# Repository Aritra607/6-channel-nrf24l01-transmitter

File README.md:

# 6-Channel nRF24L01 Wireless Transmitter

**A professional 6-channel wireless RC transmitter using Arduino Nano and nRF24L01+ RF module for remote control of drones, robots, and RC vehicles.**

> Built at **National Institute of Technology Agartala** | Apr 2025 - Present

---

## 📸 Project Gallery

The system provides precision analog control with reliable 2.4 GHz wireless communication.

| **3D PCB View** | **PCB Layout** | **Circuit Schematic** |
|:---:|:---:|:---:|
|  |  |  |
| *3D render of transmitter PCB* | *Double-sided PCB design* | *Complete circuit diagram* |
| **Transmitter** | **Receiver** |
|:---:|:---:|
|  |  |
| *Transmitter Front* | *Receiver Front* |

---

## 🛠️ Hardware Components

The transmitter is built around the Arduino Nano platform with nRF24L01+ RF module for robust wireless communication.

### Core Components

| Component | Specification | Quantity | Description |
| :--- | :--- | :---: | :--- |
| **Microcontroller** | Arduino Nano (ATmega328P) | 1 | 5V/16MHz processing |
| **RF Module** | nRF24L01+ | 1 | 2.4 GHz transceiver |
| **Joysticks** | Dual-axis analog | 3 | 6-axis control input |
| **Power Supply** | 5V regulated | 1 | USB or 7-12V battery input |
| **Decoupling Capacitors** | 10µF + 100nF | Multiple | Power stability for nRF24L01 |

### Input Configuration

| Channel | Analog Pin | Function | Control Type |
|:-------:|:----------:|:---------|:-------------|
| **CH1** | A0 | Throttle | Joystick Y-axis |
| **CH2** | A1 | Yaw | Joystick X-axis |
| **CH3** | A2 | Pitch | Joystick Y-axis |
| **CH4** | A3 | Roll | Joystick X-axis |
| **CH5** | A6 | AUX1 | Joystick Y-axis / Potentiometer |
| **CH6** | A7 | AUX2 | Joystick Y-axis / Potentiometer |

---

## 🚀 Key Features

* **6-Channel Control:** Full 6-axis control for complex RC applications
* **2.4 GHz Communication:** nRF24L01+ module with 100+ meter range (with antenna)
* **Low Latency:** 250 kbps data rate for responsive control
* **Precision Input:** 8-bit resolution (0-255) per channel
* **Auto Calibration:** Software joystick center-point mapping
* **Failsafe Mode:** Automatic safe position on signal loss
* **Low Power:** Efficient power consumption for extended battery life
* **Bi-directional Capable:** nRF24L01 supports two-way communication (receiver can send telemetry back)
* **Pipe Addressing:** Unique 40-bit address prevents crosstalk between multiple systems
* **SPI Communication:** Fast interfacing with Arduino

---

## 🏗️ Technical Architecture

The system uses the **nRF24L01+ RF module** with Arduino Nano for digital wireless data transmission.

### System Operation Flow

1. **Analog Reading:** Arduino reads 6 analog inputs from joysticks (A0-A3, A6, A7)
2. **Data Mapping:** Raw ADC values (0-1023) mapped to 0-255 range with center calibration
3. **Packet Formation:** Six 8-bit values packed into Signal structure (6 bytes total)
4. **RF Transmission:** nRF24L01 transmits packet at 250 kbps via 2.4 GHz radio
5. **Continuous Loop:** Transmitter sends updated data continuously (~100 Hz typical)

### Communication Protocol

**Pipe Address:** `0xE9E8F0F0E1LL` (40-bit unique identifier)
**Data Rate:** 250 kbps (long range mode)
**Power Level:** RF24_PA_HIGH (maximum transmission power)
**Auto-Acknowledgment:** Disabled for minimal latency
**Packet Size:** 6 bytes per transmission

### Signal Structure

```cpp
struct Signal {
  byte throttle;  // 0-255 (12 = motor stop on signal loss)
  byte pitch;     // 0-255 (127 = center)
  byte roll;      // 0-255 (127 = center)
  byte yaw;       // 0-255 (127 = center)
  byte aux1;      // 0-255 (127 = center)
  byte aux2;      // 0-255 (127 = center)
};
```

### Failsafe Configuration

On signal loss, receiver defaults to:
- **Throttle:** 12 (motor stop)
- **All other channels:** 127 (center position)

---

## 💻 Getting Started

### Prerequisites

* **Arduino IDE** (1.8.x or later) - [Download here](https://www.arduino.cc/en/software)
* **RF24 Library** by TMRh20 - Install via Library Manager
* **Arduino Nano** with USB cable
* **nRF24L01+ Module** (preferably with external antenna)
* Basic soldering equipment
* 6 analog joysticks or potentiometers
* 5V regulated power supply

### 1. Clone the Repository

```bash
git clone https://github.com/Aritra607/6-channel-nrf24l01-transmitter.git
cd 6-channel-nrf24l01-transmitter
```

### 2. Install Arduino Libraries

#### Method 1: Arduino Library Manager (Recommended)

1. Open Arduino IDE
2. Go to **Sketch → Include Library → Manage Libraries**
3. Search for "RF24"
4. Install **"RF24 by TMRh20"**
5. Restart Arduino IDE

#### Method 2: Manual Installation

```bash
cd ~/Documents/Arduino/libraries/
git clone https://github.com/nRF24/RF24.git
```

### 3. Hardware Assembly

#### 3.1 nRF24L01 to Arduino Nano Wiring

| nRF24L01 Pin | Arduino Nano Pin | Description |
|:------------:|:----------------:|:------------|
| VCC | 3.3V | **IMPORTANT: 3.3V ONLY!** |
| GND | GND | Ground |
| CE | D9 | Chip Enable |
| CSN | D10 | SPI Chip Select |
| SCK | D13 | SPI Clock |
| MOSI | D11 | SPI Master Out |
| MISO | D12 | SPI Master In |
| IRQ | Not connected | Interrupt (optional) |

**⚠️ CRITICAL:** nRF24L01 operates at **3.3V only**. Connecting to 5V will damage the module!

**Power Stability:**
- Add 10µF electrolytic capacitor between VCC and GND (near nRF24L01)
- Add 100nF ceramic capacitor between VCC and GND
- Use short wires to minimize voltage drop

#### 3.2 Joystick Connections

Connect 3 dual-axis analog joysticks to Arduino analog pins:

| Joystick | X-Axis Pin | Y-Axis Pin | VCC | GND | Function |
|:--------:|:----------:|:----------:|:---:|:---:|:---------|
| **Joystick 1** | A1 | A0 | 5V | GND | Yaw (X) / Throttle (Y) |
| **Joystick 2** | A3 | A2 | 5V | GND | Roll (X) / Pitch (Y) |
| **Joystick 3** | A7 | A6 | 5V | GND | AUX2 (X) / AUX1 (Y) |

**Note:** Potentiometers can be used instead of joysticks for AUX channels.

### 4. Software Setup

#### 4.1 Upload Transmitter Code

1. Open `transmitter.ino` in Arduino IDE
2. Select **Tools → Board → Arduino Nano**
3. Select **Tools → Processor → ATmega328P (Old Bootloader)** if needed
4. Select correct COM port under **Tools → Port**
5. Click **Upload** (Ctrl+U)

#### 4.2 Configure Pipe Address

⚠️ **IMPORTANT:** The pipe address in transmitter code **MUST** match the receiver:

```cpp
const uint64_t pipeOut = 0xE9E8F0F0E1LL;
```

If you have multiple systems operating nearby, change this address to a unique value on both TX and RX.

#### 4.3 Calibrate Joysticks

The code auto-calibrates joystick center points. If you experience drift:

1. Measure actual analog values using Serial Monitor:
   ```cpp
   Serial.begin(9600);
   Serial.println(analogRead(A0)); // Repeat for each channel
   ```

2. Adjust mapping values in code:
   ```cpp
   // Example: If your joystick reads 510-515 at center instead of 524
   data.throttle = mapJoystickValues(analogRead(A0), 12, 512, 1020, true);
   ```

3. Test all channels and adjust `lower`, `middle`, `upper` values as needed

### 5. Testing & Verification

#### 5.1 Power-On Test

1. Connect Arduino Nano to USB power
2. **Green LED** on Arduino should light up (power indicator)
3. **Green LED** on nRF24L01 should light up

#### 5.2 Transmission Test (requires receiver)

1. Build or acquire compatible receiver (see Receiver section below)
2. Power on both transmitter and receiver
3. Move joysticks and verify receiver response
4. Test all 6 channels individually
5. Test failsafe by powering off transmitter

#### 5.3 Range Test

1. Start with units 1 meter apart
2. Gradually increase distance
3. Monitor signal reliability
4. Expected range: **100+ meters** with external antenna in open space
5. **50+ meters** with built-in PCB antenna

---

## 📂 Project Structure

```
6-channel-nrf24l01-transmitter/
│
├── transmitter/
│   ├── transmitter.ino              # Main Arduino sketch
│   ├── Gerber_files/                # PCB manufacturing files
│   │   ├── *.GTL                    # Top copper layer
│   │   ├── *.GBL                    # Bottom copper layer
│   │   ├── *.GTO                    # Top silkscreen
│   │   ├── *.GBO                    # Bottom silkscreen
│   │   ├── *.GTS                    # Top soldermask
│   │   ├── *.GBS                    # Bottom soldermask
│   │   └── *.TXT                    # Drill file
│   │
│   └── images/
│       ├── 3D-VIEW.png              # 3D PCB render
│       ├── PCB.png                  # PCB layout view
│       └── Schematics.png           # Circuit schemati
│
├── docs/
│   ├── datasheets/
│   │   ├── nRF24L01.pdf            # RF module datasheet
│   │   ├── ATmega328P.pdf          # Microcontroller datasheet
│   │   └── RF24_Library.pdf        # Library documentation
│   │
│   ├── ASSEMBLY_GUIDE.md            # Detailed build instructions
│   ├── CALIBRATION.md               # Joystick calibration guide
│   ├── PCB_FABRICATION.md           # PCB ordering guide
│   └── TROUBLESHOOTING.md           # Common issues and fixes
│
├── hardware/
│   ├── BOM.md                       # Bill of materials
│   └── transmitter.kicad_pcb        # KiCad PCB design file
│
├── README.md                         # This file
├── LICENSE                           # MIT License
└── .gitignore
```

---

## 🔐 Communication Protocol Details

### nRF24L01+ Configuration

```cpp
radio.setAutoAck(false);           // Disabled for low latency
radio.setDataRate(RF24_250KBPS);   // Long range, lower speed
radio.setPALevel(RF24_PA_HIGH);    // Maximum transmission power
radio.stopListening();             // TX mode only
```

### Channel Mapping Logic

The `mapJoystickValues()` function provides:
- **Dead-zone compensation:** Smooth center-point handling
- **Range calibration:** Maps 10-bit ADC (0-1023) to 8-bit output (0-255)
- **Direction reversal:** Configurable per channel via boolean flag
- **Boundary protection:** Constrain prevents out-of-range values

**Mapping Parameters:**
- `lower`: Minimum joystick ADC value (typically 12)
- `middle`: Center position ADC value (typically 512-524)
- `upper`: Maximum joystick ADC value (typically 1020-1023)
- `reverse`: Invert signal direction (true/false)

### Data Packet Format

Each transmission contains 6 bytes:

```
Byte 0: Throttle (0-255)
Byte 1: Pitch    (0-255)
Byte 2: Roll     (0-255)
Byte 3: Yaw      (0-255)
Byte 4: AUX1     (0-255)
Byte 5: AUX2     (0-255)
```

Transmission rate: ~100 packets/second

---

## 💡 Applications

### 1. **Quadcopter/Drone Control**
Full 6-channel control for throttle, pitch, roll, yaw, plus two auxiliary channels for camera gimbal, lights, or flight modes.

### 2. **RC Car/Tank**
Control steering, throttle, and additional functions like headlights, horn, or weapon systems.

### 3. **Robotic Arm**
Simultaneous control of multiple servo motors for precise manipulation.

### 4. **Camera Gimbal**
Multi-axis camera stabilization and positioning control.

### 5. **RC Boat**
Throttle, rudder control, and auxiliary functions for navigation lights or bilge pump.

### 6. **Educational Platform**
Learn wireless communication, embedded systems, and control systems fundamentals.

---

## 📡 Receiver Setup

This transmitter requires a compatible receiver. Here's a basic receiver code structure:

```cpp
#include <SPI.h>
#include <nRF24L01.h>
#include <RF24.h>
#include <Servo.h>

const uint64_t pipeIn = 0xE9E8F0F0E1LL; // Must match transmitter!
RF24 radio(9, 10);

struct Signal {
  byte throttle;
  byte pitch;
  byte roll;
  byte yaw;
  byte aux1;
  byte aux2;
};

Signal data;
Servo servo1, servo2, servo3, servo4, servo5, servo6;

void setup() {
  radio.begin();
  radio.openReadingPipe(1, pipeIn);
  radio.setAutoAck(false);
  radio.setDataRate(RF24_250KBPS);
  radio.setPALevel(RF24_PA_HIGH);
  radio.startListening(); // Receiver mode
  
  // Attach servos to PWM pins
  servo1.attach(3);  // Throttle/ESC
  servo2.attach(4);  // Pitch
  servo3.attach(5);  // Roll
  servo4.attach(6);  // Yaw
  servo5.attach(7);  // AUX1
  servo6.attach(8);  // AUX2
}

void loop() {
  if (radio.available()) {
    radio.read(&data, sizeof(Signal));
    
    // Map 0-255 to servo pulse width (1000-2000 µs)
    servo1.writeMicroseconds(map(data.throttle, 0, 255, 1000, 2000));
    servo2.writeMicroseconds(map(data.pitch, 0, 255, 1000, 2000));
    servo3.writeMicroseconds(map(data.roll, 0, 255, 1000, 2000));
    servo4.writeMicroseconds(map(data.yaw, 0, 255, 1000, 2000));
    servo5.writeMicroseconds(map(data.aux1, 0, 255, 1000, 2000));
    servo6.writeMicroseconds(map(data.aux2, 0, 255, 1000, 2000));
  }
}
```

**Create a separate receiver project** with this code or download from the repository.

---

## 🔧 Advanced Configuration

### Changing Transmission Power

Adjust range vs power consumption:

```cpp
// Maximum range, higher power consumption
radio.setPALevel(RF24_PA_HIGH);

// Medium range, balanced
radio.setPALevel(RF24_PA_LOW);

// Minimum power for short range
radio.setPALevel(RF24_PA_MIN);
```

### Changing Data Rate

Trade speed for range:

```cpp
// Long range, lower speed (RECOMMENDED)
radio.setDataRate(RF24_250KBPS);

// Balanced
radio.setDataRate(RF24_1MBPS);

// Short range, high speed
radio.setDataRate(RF24_2MBPS);
```

### Reversing Channel Direction

Change the `reverse` parameter in `mapJoystickValues()`:

```cpp
// Normal direction
data.throttle = mapJoystickValues(analogRead(A0), 12, 524, 1020, false);

// Reversed direction
data.throttle = mapJoystickValues(analogRead(A0), 12, 524, 1020, true);
```

### Custom Failsafe Values

Modify `ResetData()` function:

```cpp
void ResetData() {
  data.throttle = 0;      // Full motor stop
  data.pitch = 127;       // Level flight
  data.roll = 127;        // Wings level
  data.yaw = 127;         // No rotation
  data.aux1 = 0;          // Lights off
  data.aux2 = 255;        // Emergency mode active
}
```

---

## 🛠️ Building from Source

### PCB Fabrication

1. **Download Gerber files** from `Gerber_files/` folder
2. **Upload to PCB manufacturer**:
   - Recommended: JLCPCB, PCBWay, OSH Park
   - Board thickness: 1.6mm
   - Finish: HASL or ENIG
   - Color: Your choice (green is cheapest)
3. **Order PCBs** (minimum order typically 5 pieces)
4. **Expected cost:** $2-5 for 5 PCBs + shipping

### Component Assembly

**Soldering Order:**
1. SMD components first (if any)
2. IC sockets (recommended for Arduino and nRF24L01)
3. Resistors
4. Capacitors (mind polarity on electrolytics!)
5. Pin headers for joysticks
6. Arduino Nano socket/header pins
7. nRF24L01 socket/header pins
8. Power connector

**Quality Check:**
- Visual inspection for solder bridges
- Continuity test with multimeter
- Check all power rails (3.3V and 5V)
- Verify no shorts between VCC and GND

---

## 🧪 Joystick Calibration

### Finding Center Values

1. Upload this calibration sketch:

```cpp
void setup() {
  Serial.begin(9600);
}

void loop() {
  Serial.print("A0: "); Serial.print(analogRead(A0));
  Serial.print(" | A1: "); Serial.print(analogRead(A1));
  Serial.print(" | A2: "); Serial.print(analogRead(A2));
  Serial.print(" | A3: "); Serial.print(analogRead(A3));
  Serial.print(" | A6: "); Serial.print(analogRead(A6));
  Serial.print(" | A7: "); Serial.println(analogRead(A7));
  delay(200);
}
```

2. Open Serial Monitor (9600 baud)
3. Center all joysticks
4. Note the center values (typically 500-530)
5. Move joysticks to extremes and note min/max values

### Updating Calibration

Replace values in main code:

```cpp
// Example: If your joystick center reads 515 instead of 524
data.throttle = mapJoystickValues(analogRead(A0), 10, 515, 1023, true);
```

---

## 🔍 Troubleshooting

| **Problem** | **Possible Cause** | **Solution** |
|-------------|-------------------|--------------|
| Transmitter not powering on | Power supply issue | Check USB connection or battery voltage |
| No RF transmission | nRF24L01 damaged | Check 3.3V supply, replace module if needed |
| Erratic behavior | Poor nRF24L01 power | Add 10µF + 100nF capacitors, use short wires |
| Receiver not responding | Pipe address mismatch | Verify `pipeOut` matches receiver's `pipeIn` |
| Short range (<10m) | Missing antenna | Add external antenna or use nRF24L01+PA+LNA |
| Joystick drift | Poor calibration | Re-calibrate center values using Serial Monitor |
| One channel not working | Wiring error | Check joystick connections to analog pins |
| Upload fails | Wrong board/port | Select Arduino Nano and correct COM port |
| Code won't compile | Missing RF24 library | Install RF24 library via Library Manager |
| Interference issues | Channel conflict | Change nRF24L01 channel or pipe address |

### Advanced Diagnostics

Add debug output to Serial Monitor:

```cpp
void setup() {
  Serial.begin(9600);
  radio.begin();
  
  // Check if radio hardware is responding
  if (!radio.isChipConnected()) {
    Serial.println("nRF24L01 NOT detected!");
  } else {
    Serial.println("nRF24L01 initialized successfully");
  }
}

void loop() {
  // Print channel values
  Serial.print("THR:"); Serial.print(data.throttle);
  Serial.print(" | YAW:"); Serial.print(data.yaw);
  Serial.print(" | PIT:"); Serial.print(data.pitch);
  Serial.print(" | ROL:"); Serial.print(data.roll);
  Serial.print(" | AX1:"); Serial.print(data.aux1);
  Serial.print(" | AX2:"); Serial.println(data.aux2);
  
  radio.write(&data, sizeof(Signal));
  delay(50);
}
```

---

## 🎯 Performance Specifications

| Parameter | Value | Notes |
|:----------|:------|:------|
| **Operating Frequency** | 2.400 - 2.525 GHz | ISM band, license-free |
| **Data Rate** | 250 kbps | Configured for maximum range |
| **Transmission Power** | 0 dBm (1 mW) | PA_HIGH setting |
| **Operating Range** | 100m+ (outdoor) | With external antenna |
| **Indoor Range** | 30-50m | Depends on obstacles |
| **Channel Resolution** | 8-bit (256 steps) | Per channel |
| **Update Rate** | ~100 Hz | Limited by loop speed |
| **Supply Voltage** | 5V (Arduino) / 3.3V (nRF24L01) | Regulated required |
| **Current Consumption** | ~50-80 mA | TX + Arduino + joysticks |
| **Battery Life** | 6-10 hours | With 500 mAh battery |

---

## 🔄 Adding More Channels

To expand beyond 6 channels:

1. **Add more analog inputs** (Arduino Nano has A4, A5 available)
2. **Update Signal structure**:
   ```cpp
   struct Signal {
     byte throttle;
     byte pitch;
     byte roll;
     byte yaw;
     byte aux1;
     byte aux2;
     byte aux3;  // New channel
     byte aux4;  // New channel
   };
   ```
3. **Add reading logic**:
   ```cpp
   data.aux3 = mapJoystickValues(analogRead(A4), 12, 524, 1020, false);
   data.aux4 = mapJoystickValues(analogRead(A5), 12, 524, 1020, false);
   ```
4. **Update receiver code** to match new structure

**Limitation:** nRF24L01 supports up to 32-byte payloads. This design can theoretically support up to 32 channels.

---

## 🎓 Learning Resources

### Understanding the Code

**Key Concepts:**
- **SPI Communication:** How Arduino talks to nRF24L01
- **Struct Data Packing:** Efficient data organization
- **Analog to Digital Conversion:** Reading joystick positions
- **Signal Mapping:** Converting ADC values to control range
- **Wireless Protocols:** Packet-based communication

### Recommended Reading

- [nRF24L01 Getting Started Guide](https://lastminuteengineers.com/nrf24l01-arduino-wireless-communication/)
- [RF24 Library Documentation](https://nrf24.github.io/RF24/)
- [Arduino Analog Input Tutorial](https://www.arduino.cc/en/Tutorial/BuiltInExamples/AnalogInput)
- [RC Protocol Basics](https://www.instructables.com/RC-Controller-Basics/)
- [KiCad PCB Design Tutorial](https://www.youtube.com/watch?v=vaCVh2SAZY4)

---

## 🤝 Contributing

Contributions, issues, and feature requests are welcome! Feel free to check the [issues page](https://github.com/Aritra607/6-channel-nrf24l01-transmitter/issues).

### How to Contribute

1. Fork the Project
2. Create your Feature Branch (`git checkout -b feature/AmazingFeature`)
3. Commit your Changes (`git commit -m 'Add some AmazingFeature'`)
4. Push to the Branch (`git push origin feature/AmazingFeature`)
5. Open a Pull Request

### Contribution Ideas

- Add support for LCD/OLED display showing channel values
- Implement telemetry reception (bidirectional communication)
- Create 3D-printable enclosure design
- Add battery voltage monitoring
- Develop Android/iOS companion app
- Create configuration software for PC

---

## 📊 Bill of Materials (BOM)

### Essential Components

| Qty | Component | Specification | Est. Cost | Notes |
|:---:|-----------|---------------|-----------|-------|
| 1 | Arduino Nano | ATmega328P, 5V/16MHz | $3-5 | Clone acceptable |
| 1 | nRF24L01+ | 2.4 GHz RF module | $1-2 | With PCB antenna |
| 3 | Joystick | Dual-axis analog | $1-2 each | 10kΩ potentiometers |
| 1 | Capacitor | 10µF electrolytic | $0.10 | 16V or higher |
| 2 | Capacitor | 100nF ceramic | $0.10 | Power decoupling |
| 1 | PCB | Custom transmitter PCB | $2-5 | Or use perfboard |
| - | Wire | 22-24 AWG | $2 | Stranded for joysticks |
| 1 | Power Source | 5V USB or battery | Variable | USB power bank works great |

### Optional Enhancements

| Qty | Component | Purpose | Est. Cost |
|:---:|-----------|---------|-----------|
| 1 | nRF24L01+PA+LNA | Extended range (1000m+) | $3-4 |
| 1 | 0.96" OLED Display | Show channel values | $3-5 |
| 1 | Voltage Regulator | 7805 for battery operation | $0.50 |
| 1 | Power Switch | On/off control | $0.50 |
| 6 | Trim Potentiometer | Fine-tune channel offset | $0.30 each |
| 1 | Buzzer | Low battery alarm | $1 |

**Total Estimated Cost:** 
- Basic build: **$15-20 USD**
- Enhanced build: **$30-40 USD**

---

## 🔐 Security & Best Practices

* **Unique Pipe Address:** Change default `0xE9E8F0F0E1LL` to prevent interference from nearby systems
* **Power Quality:** Always use quality regulated power supply; nRF24L01 is sensitive to voltage fluctuations
* **Proper Grounding:** Ensure common ground between all components
* **Capacitor Placement:** Place decoupling caps as close as possible to nRF24L01 VCC pin
* **Antenna Installation:** Use proper antenna for extended range (ceramic chip or external whip)
* **SPI Wiring:** Keep SPI wires short and away from power wires to reduce noise
* **Testing:** Always test failsafe mode to ensure safe behavior on signal loss
* **Battery Monitoring:** Add voltage divider to monitor battery level on A4 or A5

---

## 🌟 Future Enhancements

- [ ] Add OLED display for real-time channel monitoring
- [ ] Implement battery voltage telemetry from receiver
- [ ] Add RSSI (signal strength) indicator
- [ ] Create 3D-printed ergonomic enclosure
- [ ] Implement channel mixing (e.g., elevon mixing for flying wings)
- [ ] Add trim buttons for fine adjustments
- [ ] Develop model memory for multiple vehicles
- [ ] Add dual-rate/expo settings for control sensitivity
- [ ] Implement bind button for easy receiver pairing
- [ ] Create PC/mobile configuration software

---

## 📄 License

Distributed under the **MIT License**. See `LICENSE` file for more information.

``
MIT License - Copyright (c) 2025 Aritra Banik

Permission is hereby granted, free of charge, to any person obtaining a copy
of this software and hardware design files...
```

--

## 🔗 Resources & Reference

### Datasheets & Documentation
- [nRF24L01+ Datasheet](https://www.sparkfun.com/datasheets/Components/SMD/nRF24L01Pluss_Preliminary_Product_Specification_

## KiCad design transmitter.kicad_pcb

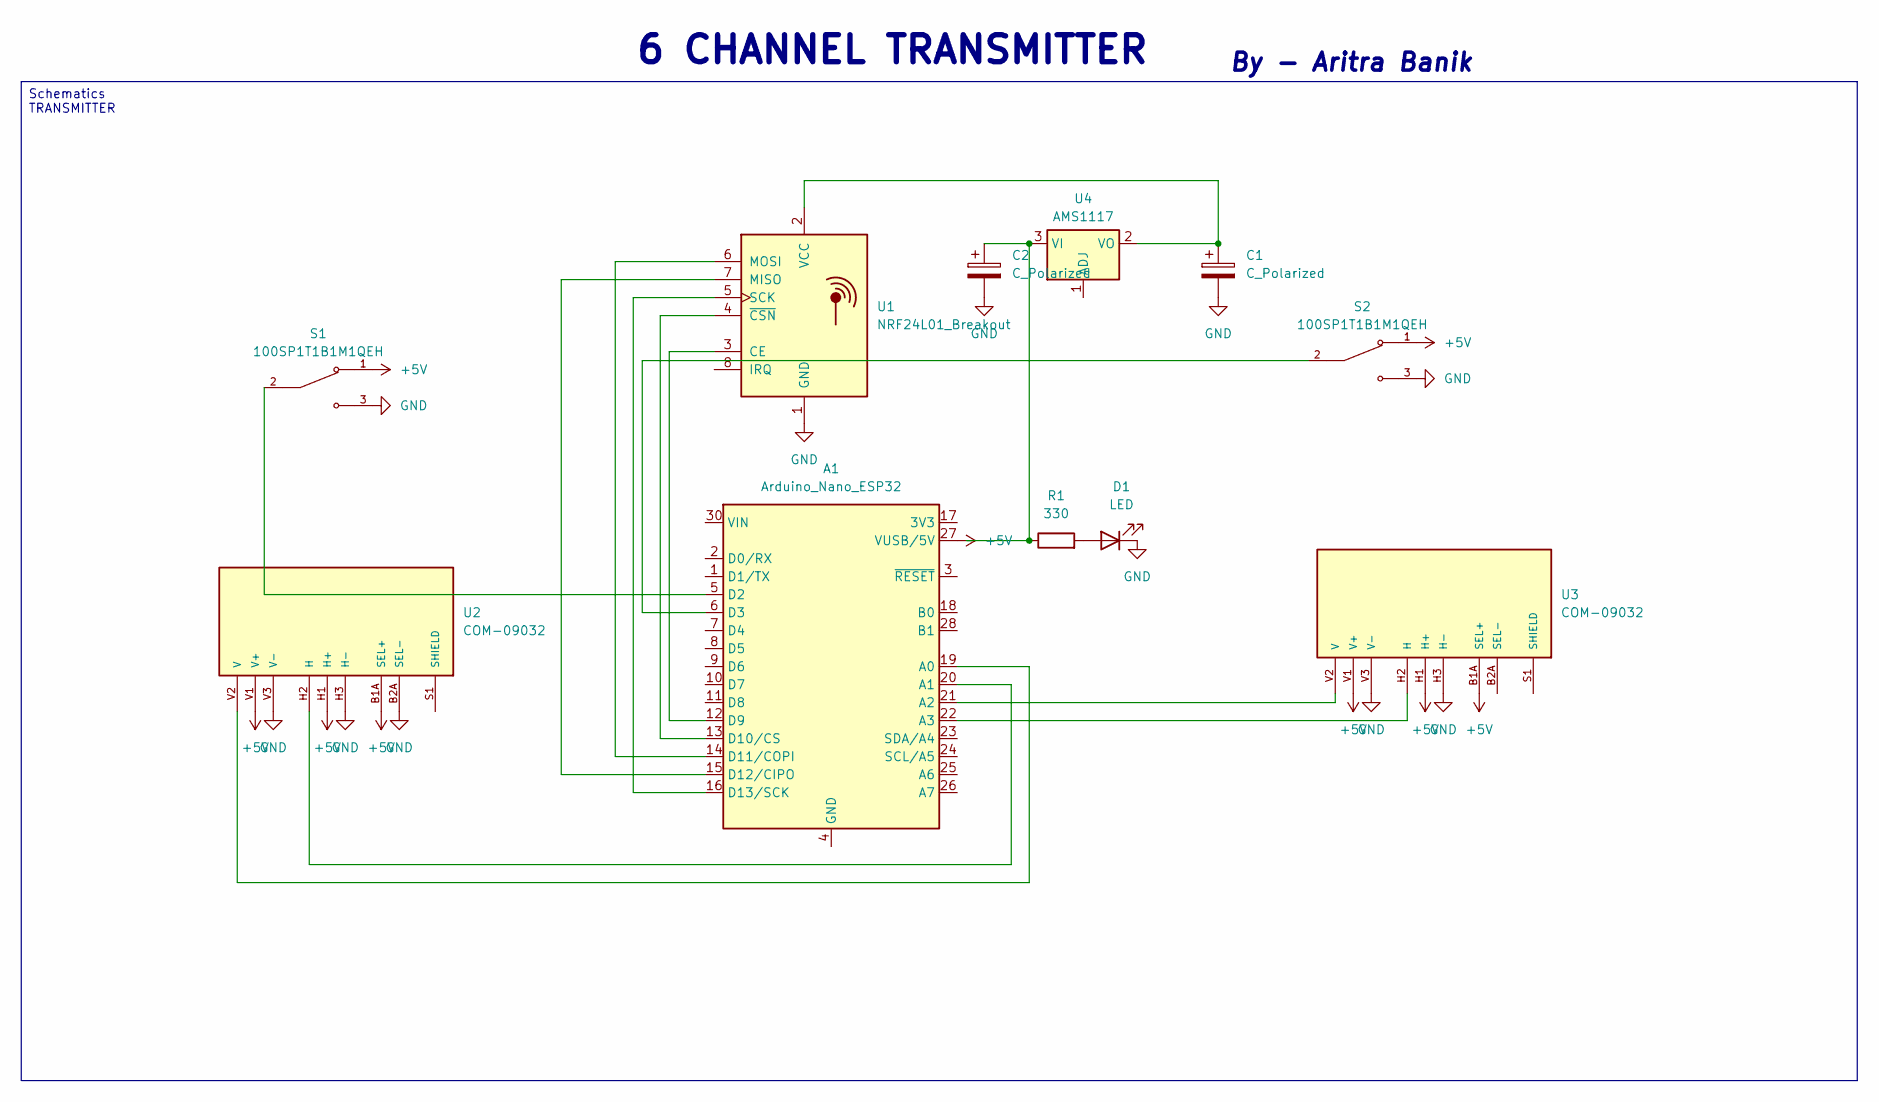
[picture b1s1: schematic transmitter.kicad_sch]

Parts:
A1: Arduino_Nano_ESP32; Arduino_Nano
C1, C2: C_Polarized; CP_Radial_D12.5mm_P2.50mm
D1: LED; LED_0805_2012Metric
R1: 330; LED_0805_2012Metric
S1, S2: 100SP1T1B1M1QEH; SW_100SP1T1B1M1QEH; PARTREV D
U1: NRF24L01_Breakout; nRF24L01_Breakout
U2, U3: COM-09032; XDCR_COM-09032; PARTREV N/A
U4: AMS1117; SOT-223-3_TabPin2

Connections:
+5V: A1.27 (VUSB/5V), S1.1, S2.1, U2.B1A (SEL+), U2.H1 (H+), U2.V1 (V+), U3.B1A (SEL+), U3.H1 (H+), U3.V1 (V+)
GND: C1.2, C2.2, D1.1 (K), S1.3, S2.3, U1.1 (GND), U2.B2A (SEL-), U2.H3 (H-), U2.V3 (V-), U3.H3 (H-), U3.V3 (V-)
unnamed: A1.19 (A0), U2.V2 (V)
unnamed: A1.20 (A1), U2.H2 (H)
unnamed: A1.21 (A2), U3.V2 (V)
unnamed: A1.22 (A3), U3.H2 (H)
unnamed: A1.5 (D2), S1.2
unnamed: A1.6 (D3), S2.2
unnamed: A1.12 (D9), U1.3 (CE)
unnamed: A1.13 (D10/CS), U1.4 (~CSN)
unnamed: A1.14 (D11/COPI), U1.6 (MOSI)
unnamed: A1.15 (D12/CIPO), U1.7 (MISO)
unnamed: A1.16 (D13/SCK), U1.5 (SCK)
unnamed: A1.4 (GND), A1.29 (GND)
unnamed: D1.2 (A), R1.2
unnamed: C1.1, U1.2 (VCC), U4.2 (VO)
unnamed: U2.S1 (SHIELD), U2.S2 (SHIELD), U2.S3 (SHIELD), U2.S4 (SHIELD)
unnamed: U3.S1 (SHIELD), U3.S2 (SHIELD), U3.S3 (SHIELD), U3.S4 (SHIELD)
unnamed: C2.1, R1.1, U4.3 (VI)

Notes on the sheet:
By - Aritra Banik
6 CHANNEL TRANSMITTER
Schematics TRANSMITTER

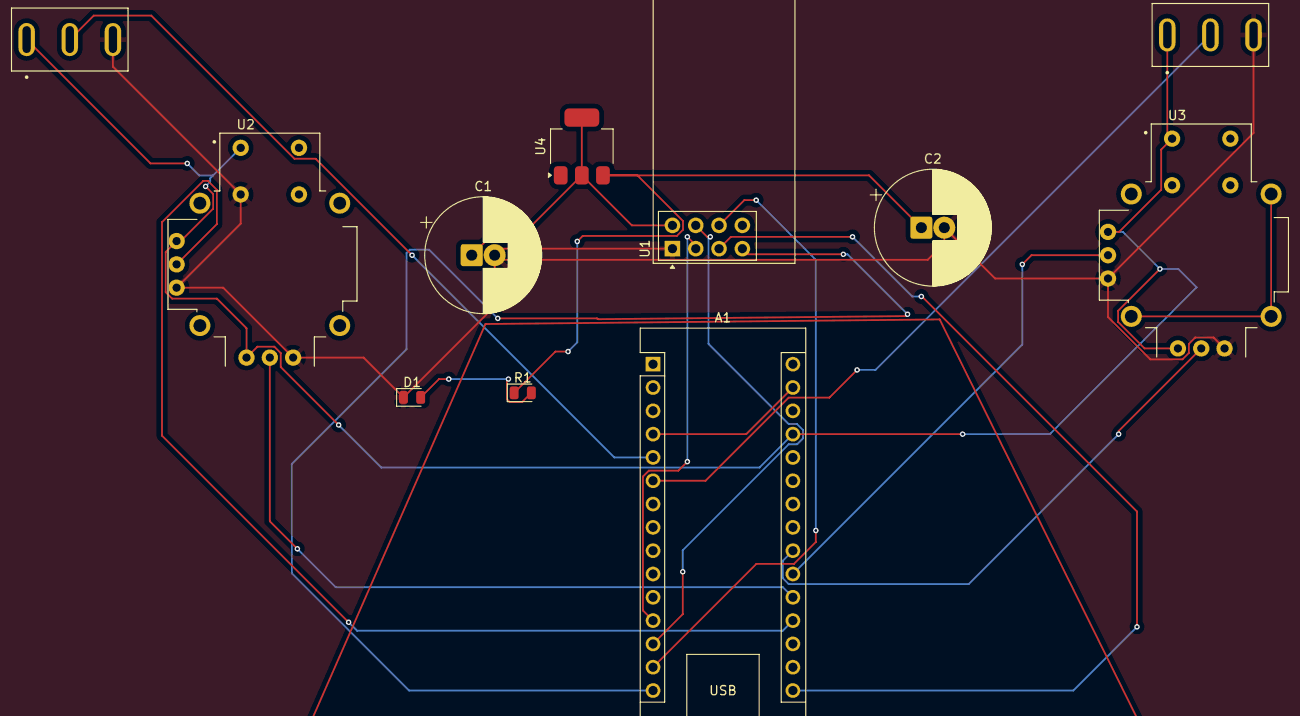
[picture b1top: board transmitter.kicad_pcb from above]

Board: 2 copper layers, 11 parts (0 on the bottom side), 19 nets.
